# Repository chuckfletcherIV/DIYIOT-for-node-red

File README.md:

# DIYIOT
Open source IOT hardware and software platform based on cheap commodity sensors, ESP8266-12e chips, the MQTT protocol and powered by IBM's Node-Red (pre-installed with most new raspberry Pi 3 installations).

The goal of the project is to put sensors (and actuators like servos or leds) on a local wifi network as inexpensively as possible, ideally for under $7 or 8 per device (including a power supply). 

Using Node-red, these devices can trigger or be triggered by any IOT activity you can think of. Node-red has dozens of supported IOT hooks to services and devices, like Hue or Lifx light bulbs, twitter integration or even the ability to send txt messages via twilio.

No coding is required for basic functionality. All data is sent to Node-red for processing and triggering. Node-red lets you do alot without coding as well, but if you need to code, you can do what you need to with simple javascript. 

DIYIOT is great for home automation projects, DIY escape rooms and halloween displays, and even interactive installations. For more permanent installations, sensors can be soldered directly into the board, vs using a header (which makes the sensor swappable). 

See DIY Board and Sensor Pin Map to figure out what board to use for which sensor (or actuator), also see notes for more advanced usage.

You can use www.PCBGOGO.com to get your own boards made for under $1 each. Gerber files are available for download from our site under "PCB". Keep an eye out for other sources for DIYIOT boards over the coming months. 

If you find a cheap commodity sensor that works great with an exisiting board - let us know so we can add it to the list.

If there is a problem with a sensor firmware code, or pin map, let us know or share a fix.

Future project goals:

Automatic Device Discovery with mDNS (bonjour)

SSL Level Security 

Smaller board size

Long term power and battery opimization

Even more cost reduction per device if we can find engineering and manufacturing partners to work with. 

Thanks, 

the DIYIOT team

Join the DIYIOT for Node Red mailing list at https://groups.google.com/forum/#!forum/diyiot-node-red

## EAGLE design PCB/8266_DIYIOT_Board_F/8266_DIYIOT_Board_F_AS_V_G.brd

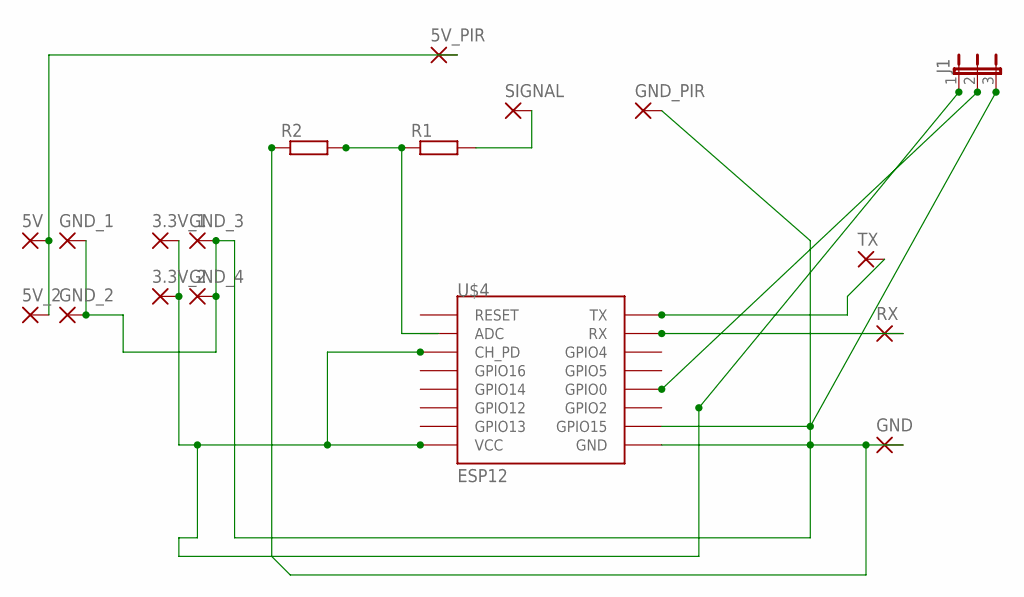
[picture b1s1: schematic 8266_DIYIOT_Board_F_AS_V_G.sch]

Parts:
3.3V_1, 3.3V_2, 5V, 5V_2, 5V_PIR: 2,15/1,0
GND: 2,15/1,0
GND_1, GND_2, GND_3, GND_4: 2,15/1,0
GND_PIR: 2,15/1,0
J1: JP2E; JP2
R1, R2: R0204/7; 0204/7
RX: 2,15/1,0
SIGNAL: 2,15/1,0
TX: 2,15/1,0
U$4: ESP12

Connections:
5V: 5V.1, 5V_2.1, 5V_PIR.1, GND.1, GND_1.1, GND_2.1, GND_3.1, GND_4.1, GND_PIR.1, J1.3, R2.1, U$4.GND, U$4.GPIO15
unnamed: J1.2, U$4.GPIO0
unnamed: R1.2, SIGNAL.1
unnamed: R1.1, R2.2, U$4.ADC
unnamed: 3.3V_1.1, 3.3V_2.1, J1.1, U$4.CH_PD, U$4.VCC
RX: RX.1, U$4.RX
TX: TX.1, U$4.TX

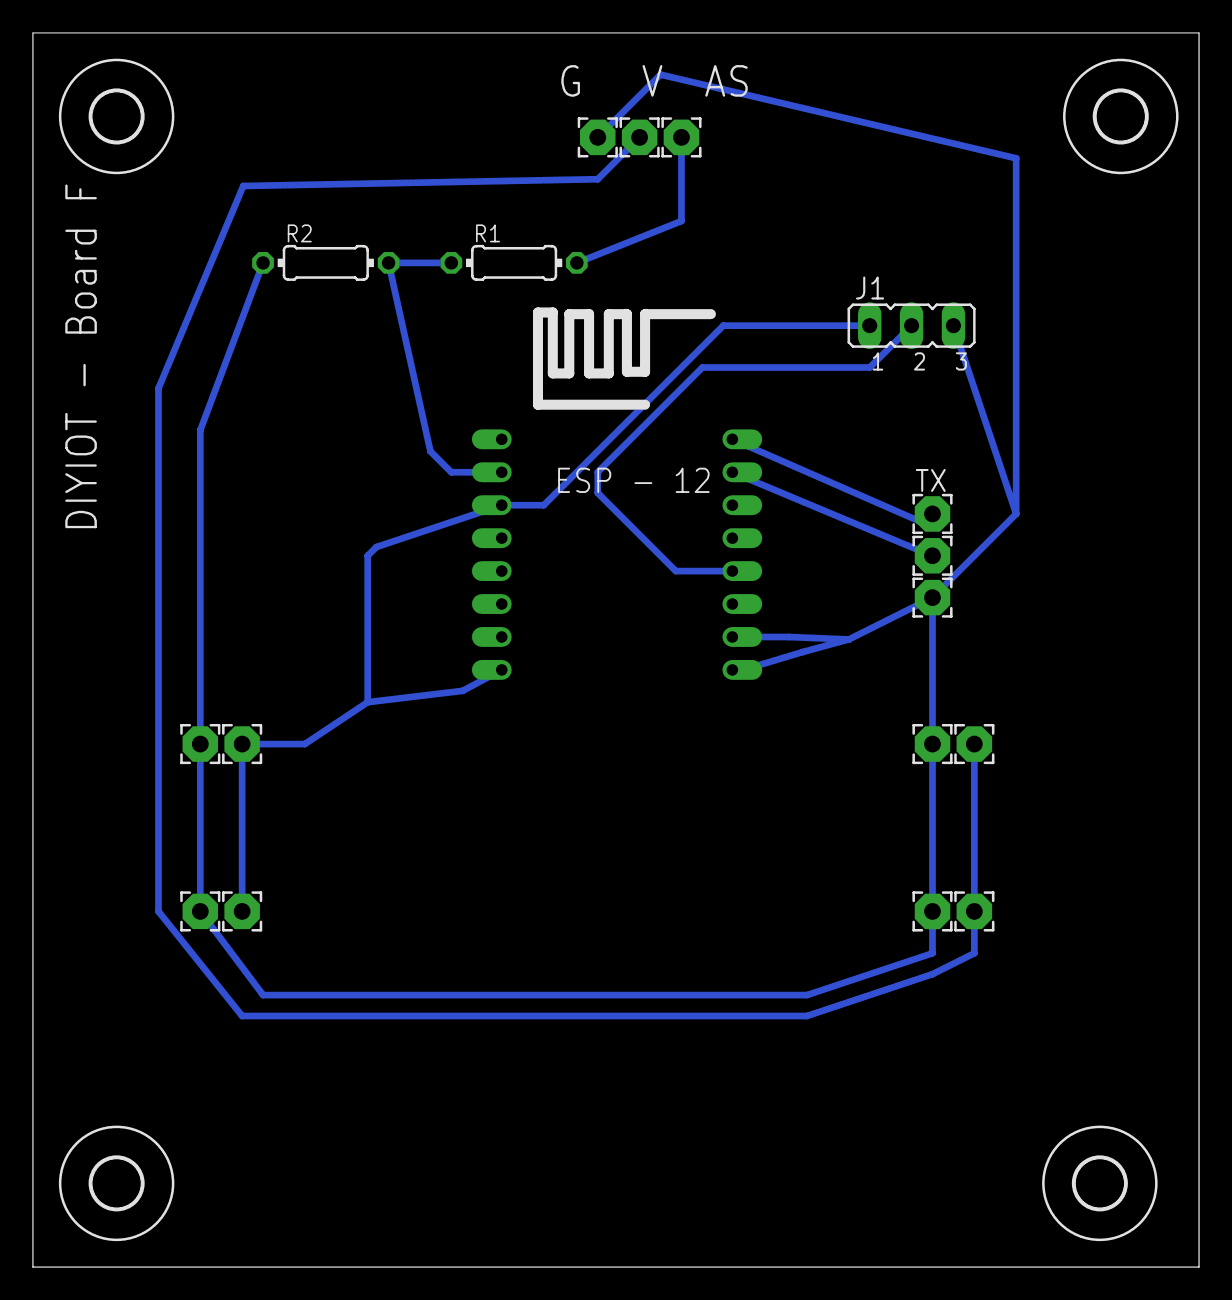
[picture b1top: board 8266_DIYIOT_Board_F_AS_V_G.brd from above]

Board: 2 copper layers, 70.8 x 74.9 mm, 22 parts (0 on the bottom side), 7 nets.

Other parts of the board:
U$1, U$2, U$5, U$6: 3,0

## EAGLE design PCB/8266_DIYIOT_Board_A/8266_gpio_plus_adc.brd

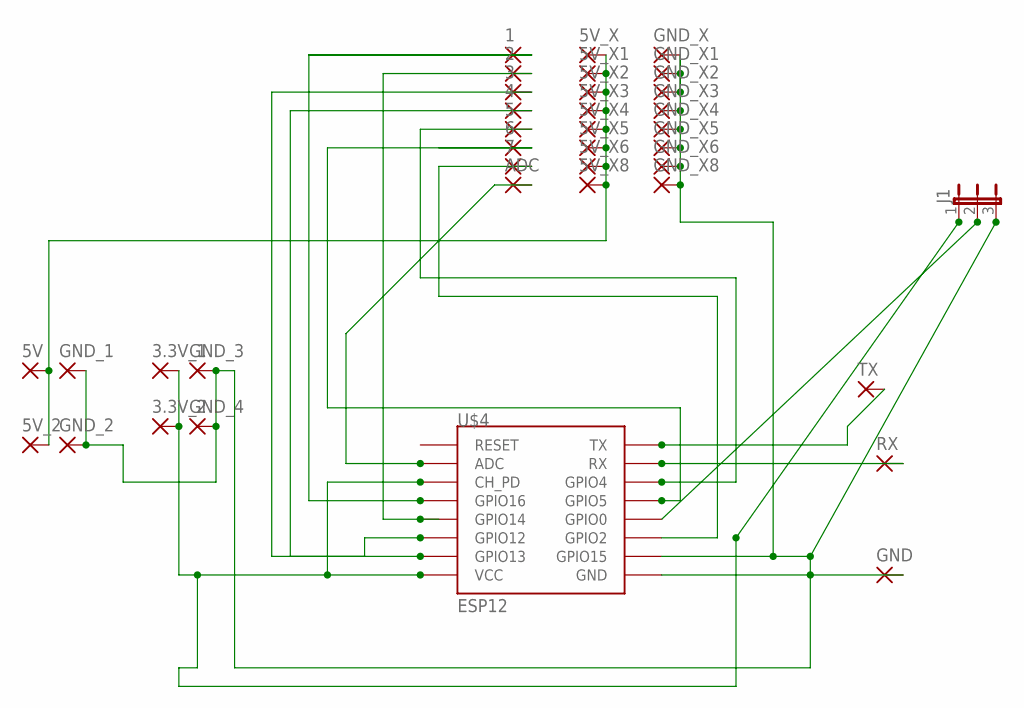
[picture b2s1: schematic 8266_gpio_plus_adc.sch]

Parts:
1, 2, 3, 3.3V_1, 3.3V_2, 4, 5, 5V, 5V_2, 5V_X, 5V_X1, 5V_X2, 5V_X3, 5V_X4, 5V_X5, 5V_X6, 5V_X8, 6, 7: 2,15/1,0
ADC: 2,15/1,0
GND: 2,15/1,0
GND_1, GND_2, GND_3, GND_4: 2,15/1,0
GND_X, GND_X1, GND_X2, GND_X3, GND_X4, GND_X5, GND_X6, GND_X8: 2,15/1,0
J1: JP2E; JP2
RX: 2,15/1,0
TX: 2,15/1,0
U$4: ESP12

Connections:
5V: 5V.1, 5V_2.1, 5V_X.1, 5V_X1.1, 5V_X2.1, 5V_X3.1, 5V_X4.1, 5V_X5.1, 5V_X6.1, 5V_X8.1
GND: GND.1, GND_1.1, GND_2.1, GND_3.1, GND_4.1, GND_X.1, GND_X1.1, GND_X2.1, GND_X3.1, GND_X4.1, GND_X5.1, GND_X6.1, GND_X8.1, J1.3, U$4.GND, U$4.GPIO15
unnamed: 2.1, U$4.GPIO14
unnamed: J1.2, U$4.GPIO0
unnamed: 3.1, U$4.GPIO12
unnamed: 4.1, U$4.GPIO13
unnamed: 3.3V_1.1, 3.3V_2.1, J1.1, U$4.CH_PD, U$4.VCC
unnamed: 1.1, U$4.GPIO16
unnamed: 7.1, U$4.GPIO2
unnamed: 6.1, U$4.GPIO5
unnamed: 5.1, U$4.GPIO4
unnamed: ADC.1, U$4.ADC
RX: RX.1, U$4.RX
TX: TX.1, U$4.TX

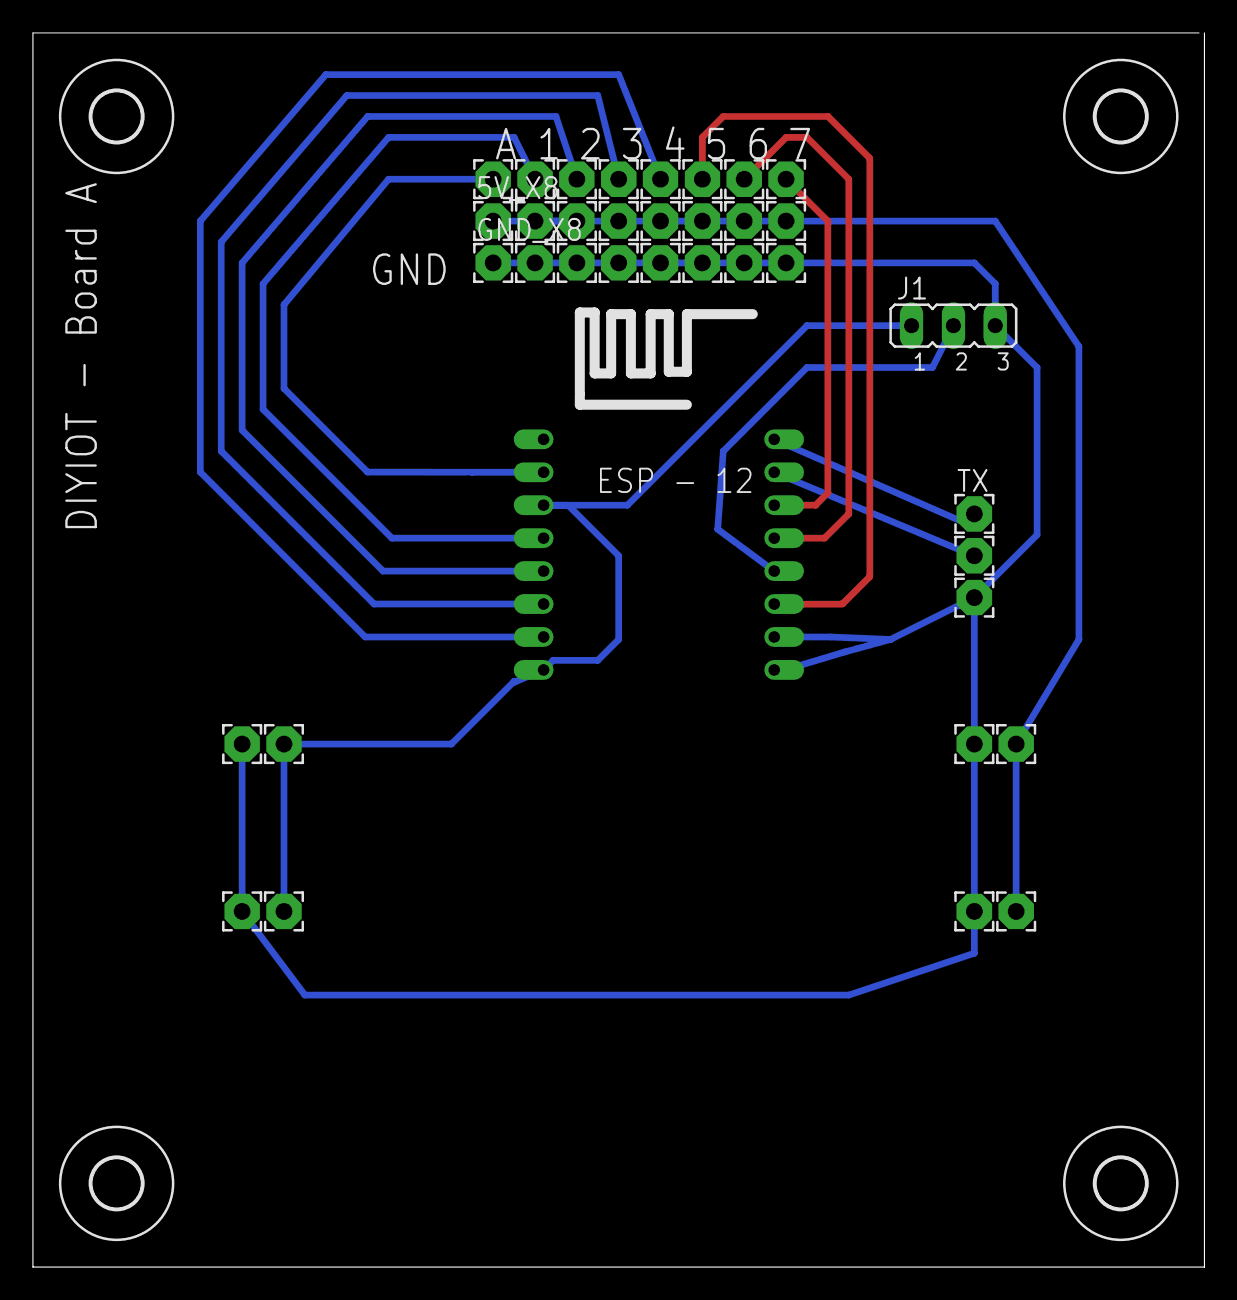
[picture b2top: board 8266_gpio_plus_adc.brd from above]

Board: 2 copper layers, 71.1 x 74.9 mm, 41 parts (0 on the bottom side), 14 nets.

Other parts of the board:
U$1, U$2, U$5, U$6: 3,0

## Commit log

2016-08-24 updated files
2016-09-12 lots of updates. Renamed and organized boards
2016-09-19 lots of updates
2016-09-19 cleaned up folders
2016-09-19 added pin map files
2016-09-19 cleaned up pin map files
2016-09-19 updated firmware status
2016-10-17 updated stuff
